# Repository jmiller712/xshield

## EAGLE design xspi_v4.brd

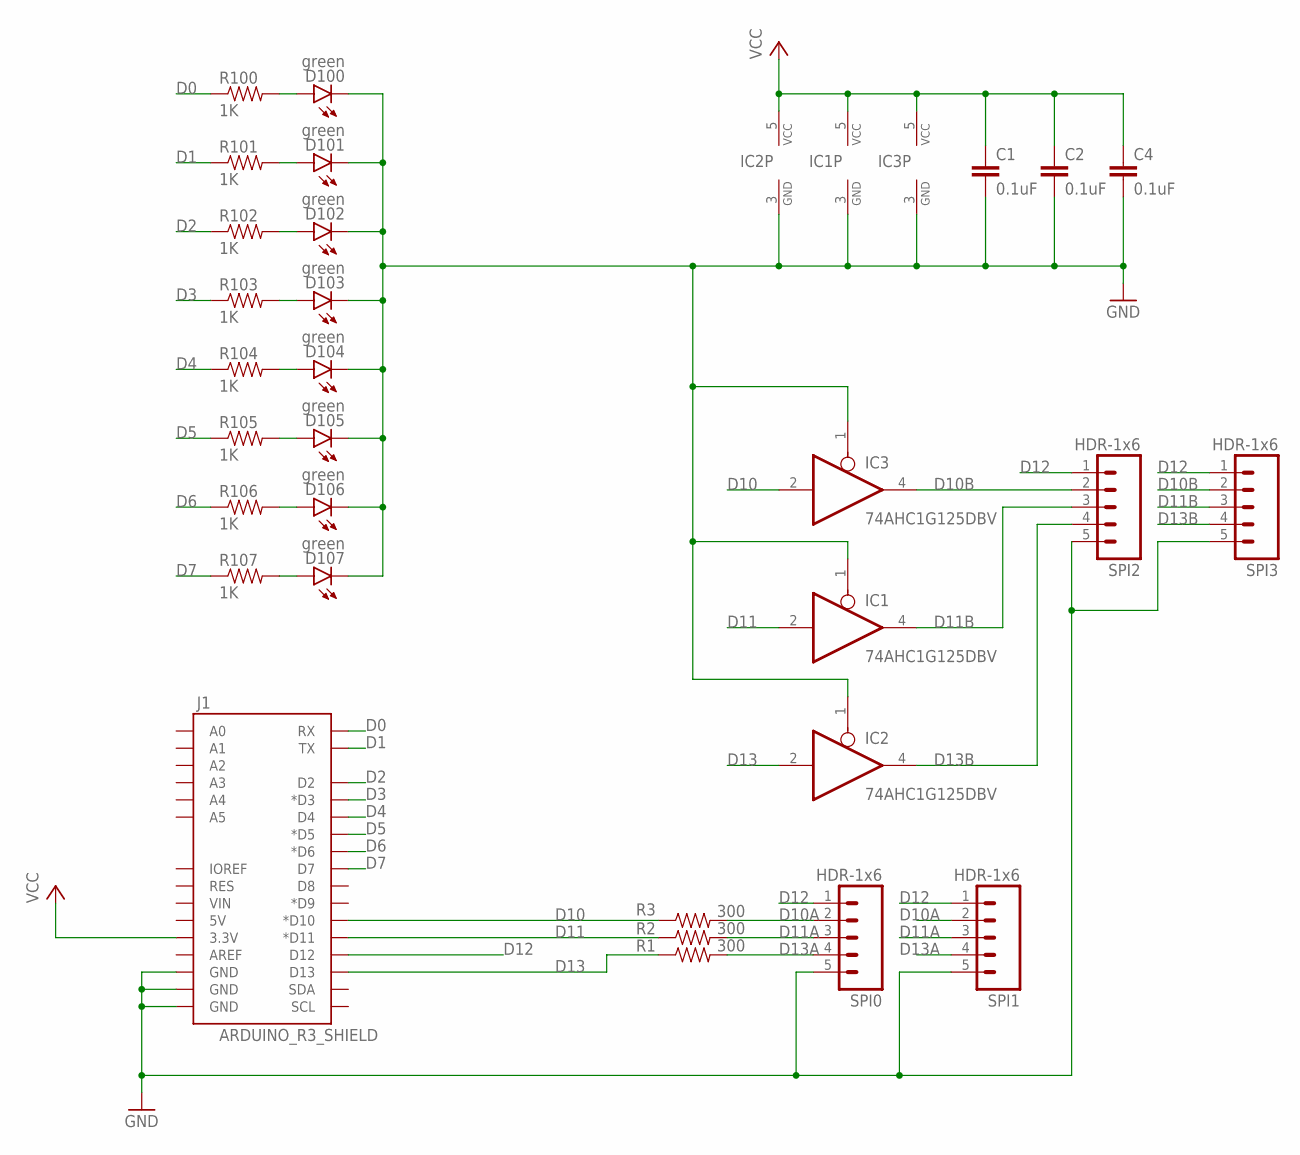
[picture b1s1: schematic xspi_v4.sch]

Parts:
C1, C2, C4: 0.1uF; 0805-CAP
D100, D101, D102, D103, D104, D105, D106, D107: green; FKIT-LED-1206
IC1, IC2, IC3: 74AHC1G125DBV; SOT23-5
J1: ARDUINO_R3_SHIELD; UNO_R3_SHIELD
R1, R2, R3: 300; AXIAL-0.4
R100, R101, R102, R103, R104, R105, R106, R107: 1K; 0805
SPI0, SPI1, SPI2, SPI3: HDR-1x6; 1X05_LONGPADS

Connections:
D0: J1.RX, R100.1
D1: J1.TX, R101.1
D2: J1.D2, R102.1
D3: J1.D3 (*D3), R103.1
D4: J1.D4, R104.1
D5: J1.D5 (*D5), R105.1
D6: J1.D6 (*D6), R106.1
D7: J1.D7, R107.1
D10: IC3.2 (I), J1.D10 (*D10), R3.P$1 (1)
D10A: R3.P$2 (2), SPI0.2, SPI1.2
D10B: IC3.4 (O), SPI2.2, SPI3.2
D11: IC1.2 (I), J1.D11 (*D11), R2.P$1 (1)
D11A: R2.P$2 (2), SPI0.3, SPI1.3
D11B: IC1.4 (O), SPI2.3, SPI3.3
D12: J1.D12, SPI0.1, SPI1.1, SPI2.1, SPI3.1
D13: IC2.2 (I), J1.D13, R1.P$1 (1)
D13A: R1.P$2 (2), SPI0.4, SPI1.4
D13B: IC2.4 (O), SPI2.4, SPI3.4
GND: C1.2, C2.2, C4.2, D100.C, D101.C, D102.C, D103.C, D104.C, D105.C, D106.C, D107.C, IC1.1 (OE), IC1.3 (GND), IC2.1 (OE), IC2.3 (GND), IC3.1 (OE), IC3.3 (GND), J1.GND@0 (GND), J1.GND@1 (GND), J1.GND@2 (GND), SPI0.5, SPI1.5, SPI2.5, SPI3.5
unnamed: D107.A, R107.2
unnamed: D106.A, R106.2
unnamed: D105.A, R105.2
unnamed: D104.A, R104.2
unnamed: D103.A, R103.2
unnamed: D102.A, R102.2
unnamed: D100.A, R100.2
unnamed: D101.A, R101.2
VCC: C1.1, C2.1, C4.1, IC1.5 (VCC), IC2.5 (VCC), IC3.5 (VCC), J1.3.3V

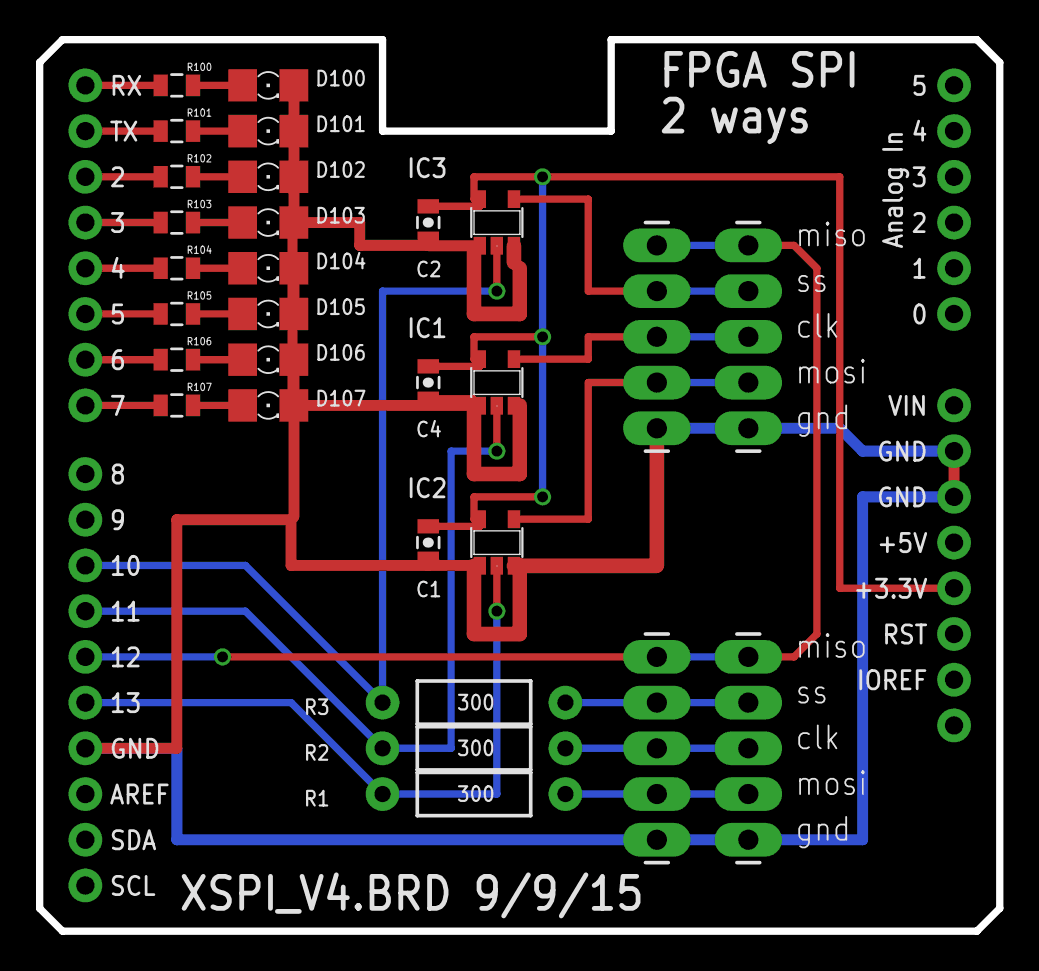
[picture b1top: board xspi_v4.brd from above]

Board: 2 copper layers, 53.3 x 49.5 mm, 30 parts (0 on the bottom side), 28 nets.

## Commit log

2015-09-02 initial commit
    spit board rev3
2015-09-02 removed ground traces
    removed superfluous ground traces
2015-09-02 visual marker
    visual flag
2015-09-06 test upload ' master
2015-09-07 version 4
2015-09-09 oshpark xspi_v4

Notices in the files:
parts and their libraries:
SparkFun-Boards: Licensing: Creative Commons ShareAlike 4.0 International - https://creativecommons.org/licenses/by-sa/4.0
